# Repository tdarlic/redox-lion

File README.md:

# redox-lion
Wireless redox keyboard based on nRF52840 or similar chips and with lion battery

Chip purchased for BL is: [MS88SF2 Ultra-low Power Wireless BLE 5.0 Module](https://www.aliexpress.com/item/4000101935456.html)
Product page is [here](https://en.minewsemi.com/bluetooth-module/nrf52840ms88sf21)

## Inspiration
- [Wubbo](https://github.com/cacheworks/Wubbo)
- [Dao Choc BLE Keyboard](https://github.com/yumagulovrn/dao-choc-ble)
- [le_chiff_ble](https://github.com/MangoIV/le_chiff_ble) by [MangoIV](https://github.com/MangoIV) - electrical circuit

### Various links
(BlueMicro840 V1.x)[http://nrf52.jpconstantineau.com/docs/bluemicro840_v1/]

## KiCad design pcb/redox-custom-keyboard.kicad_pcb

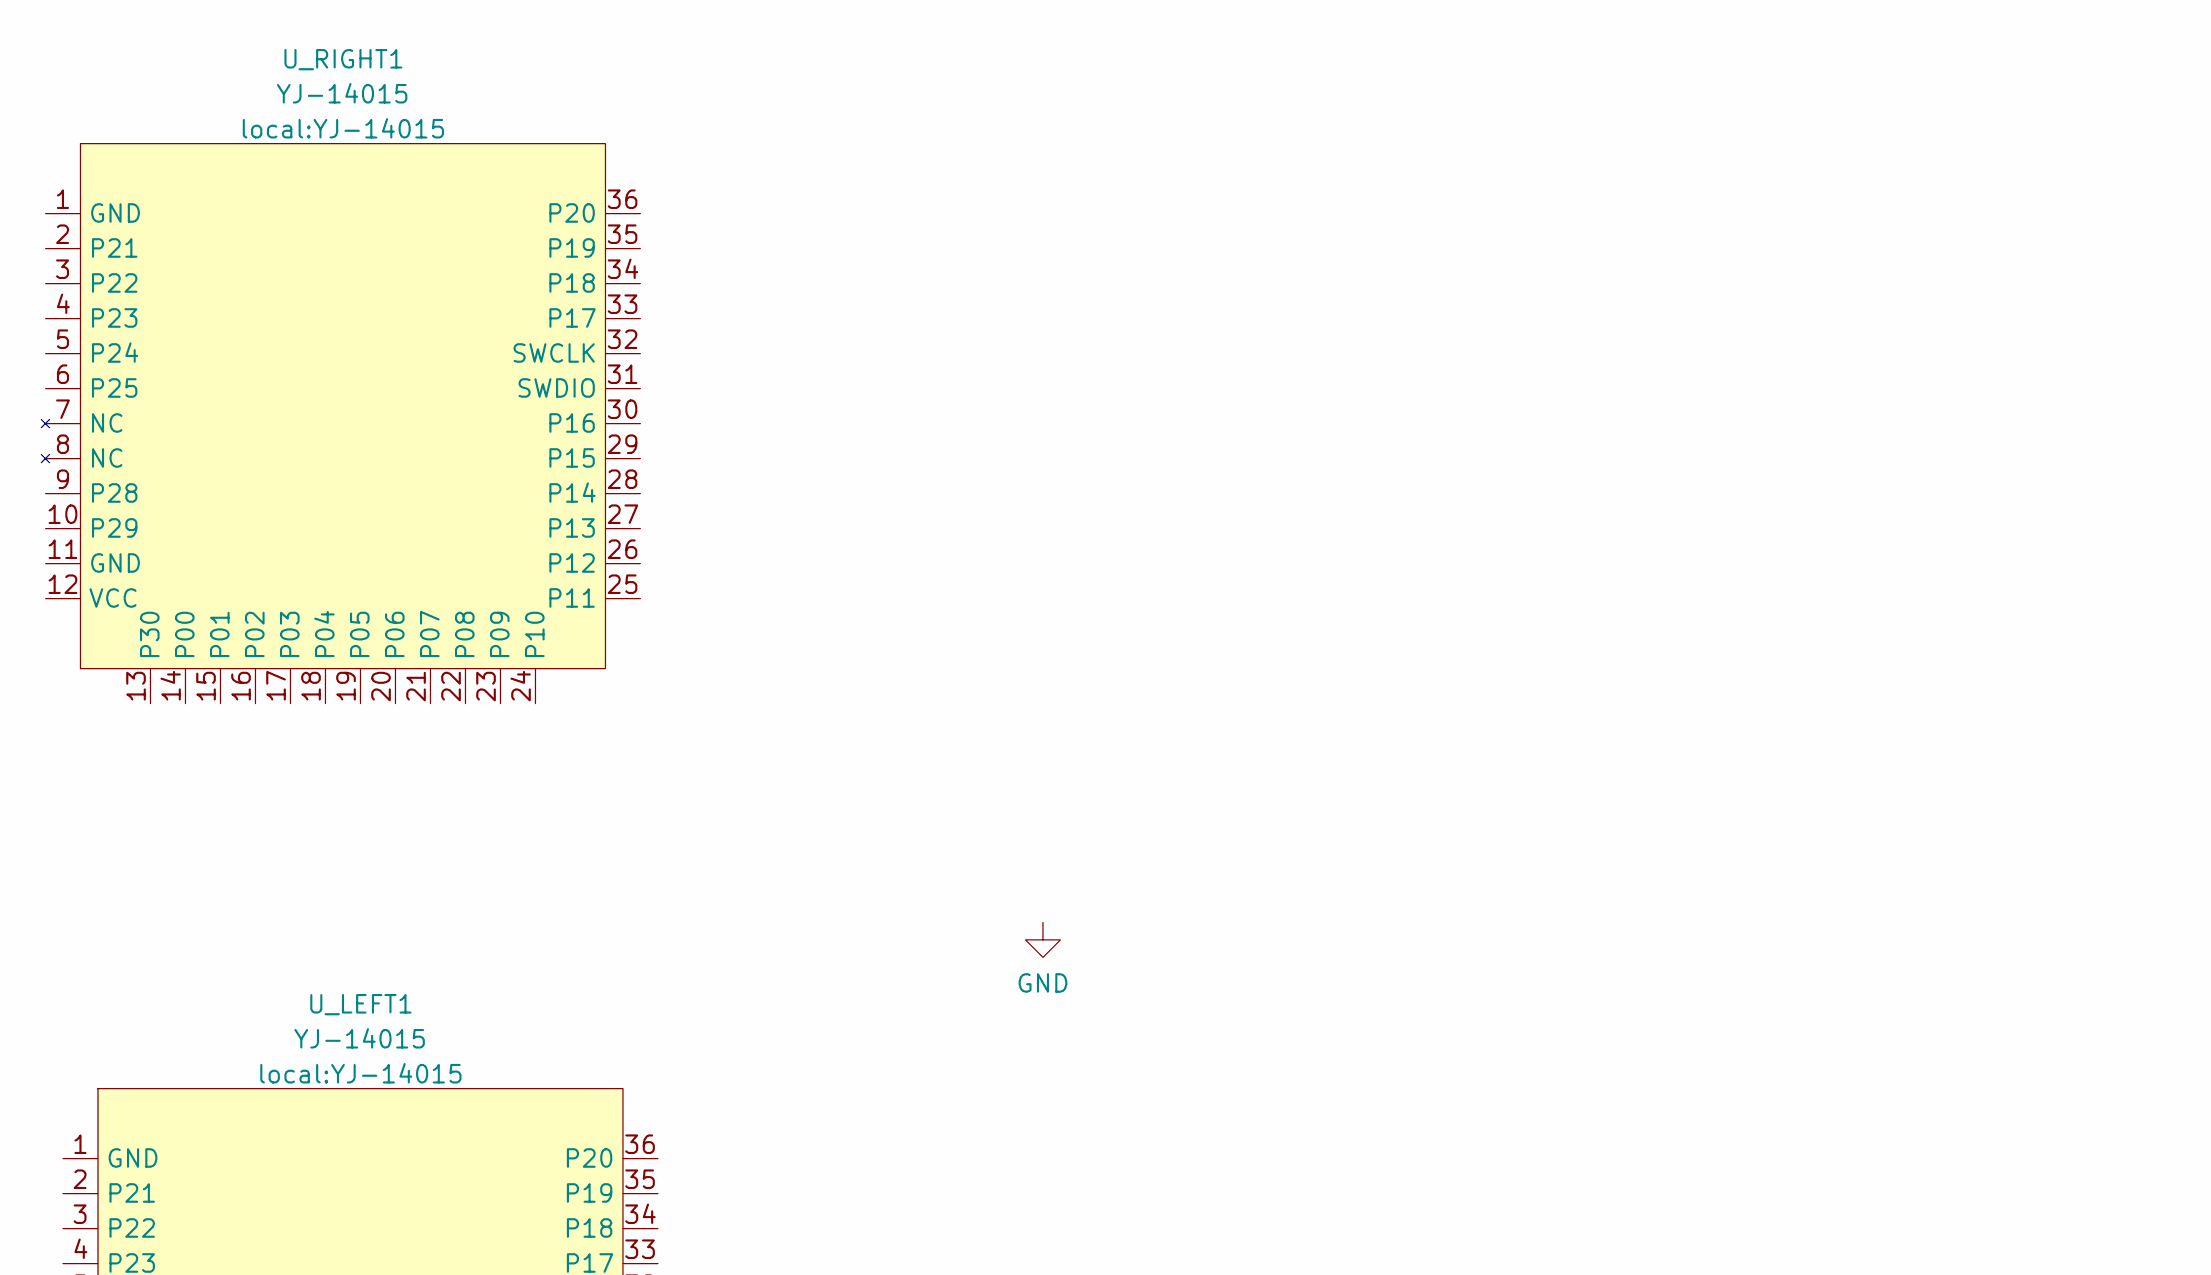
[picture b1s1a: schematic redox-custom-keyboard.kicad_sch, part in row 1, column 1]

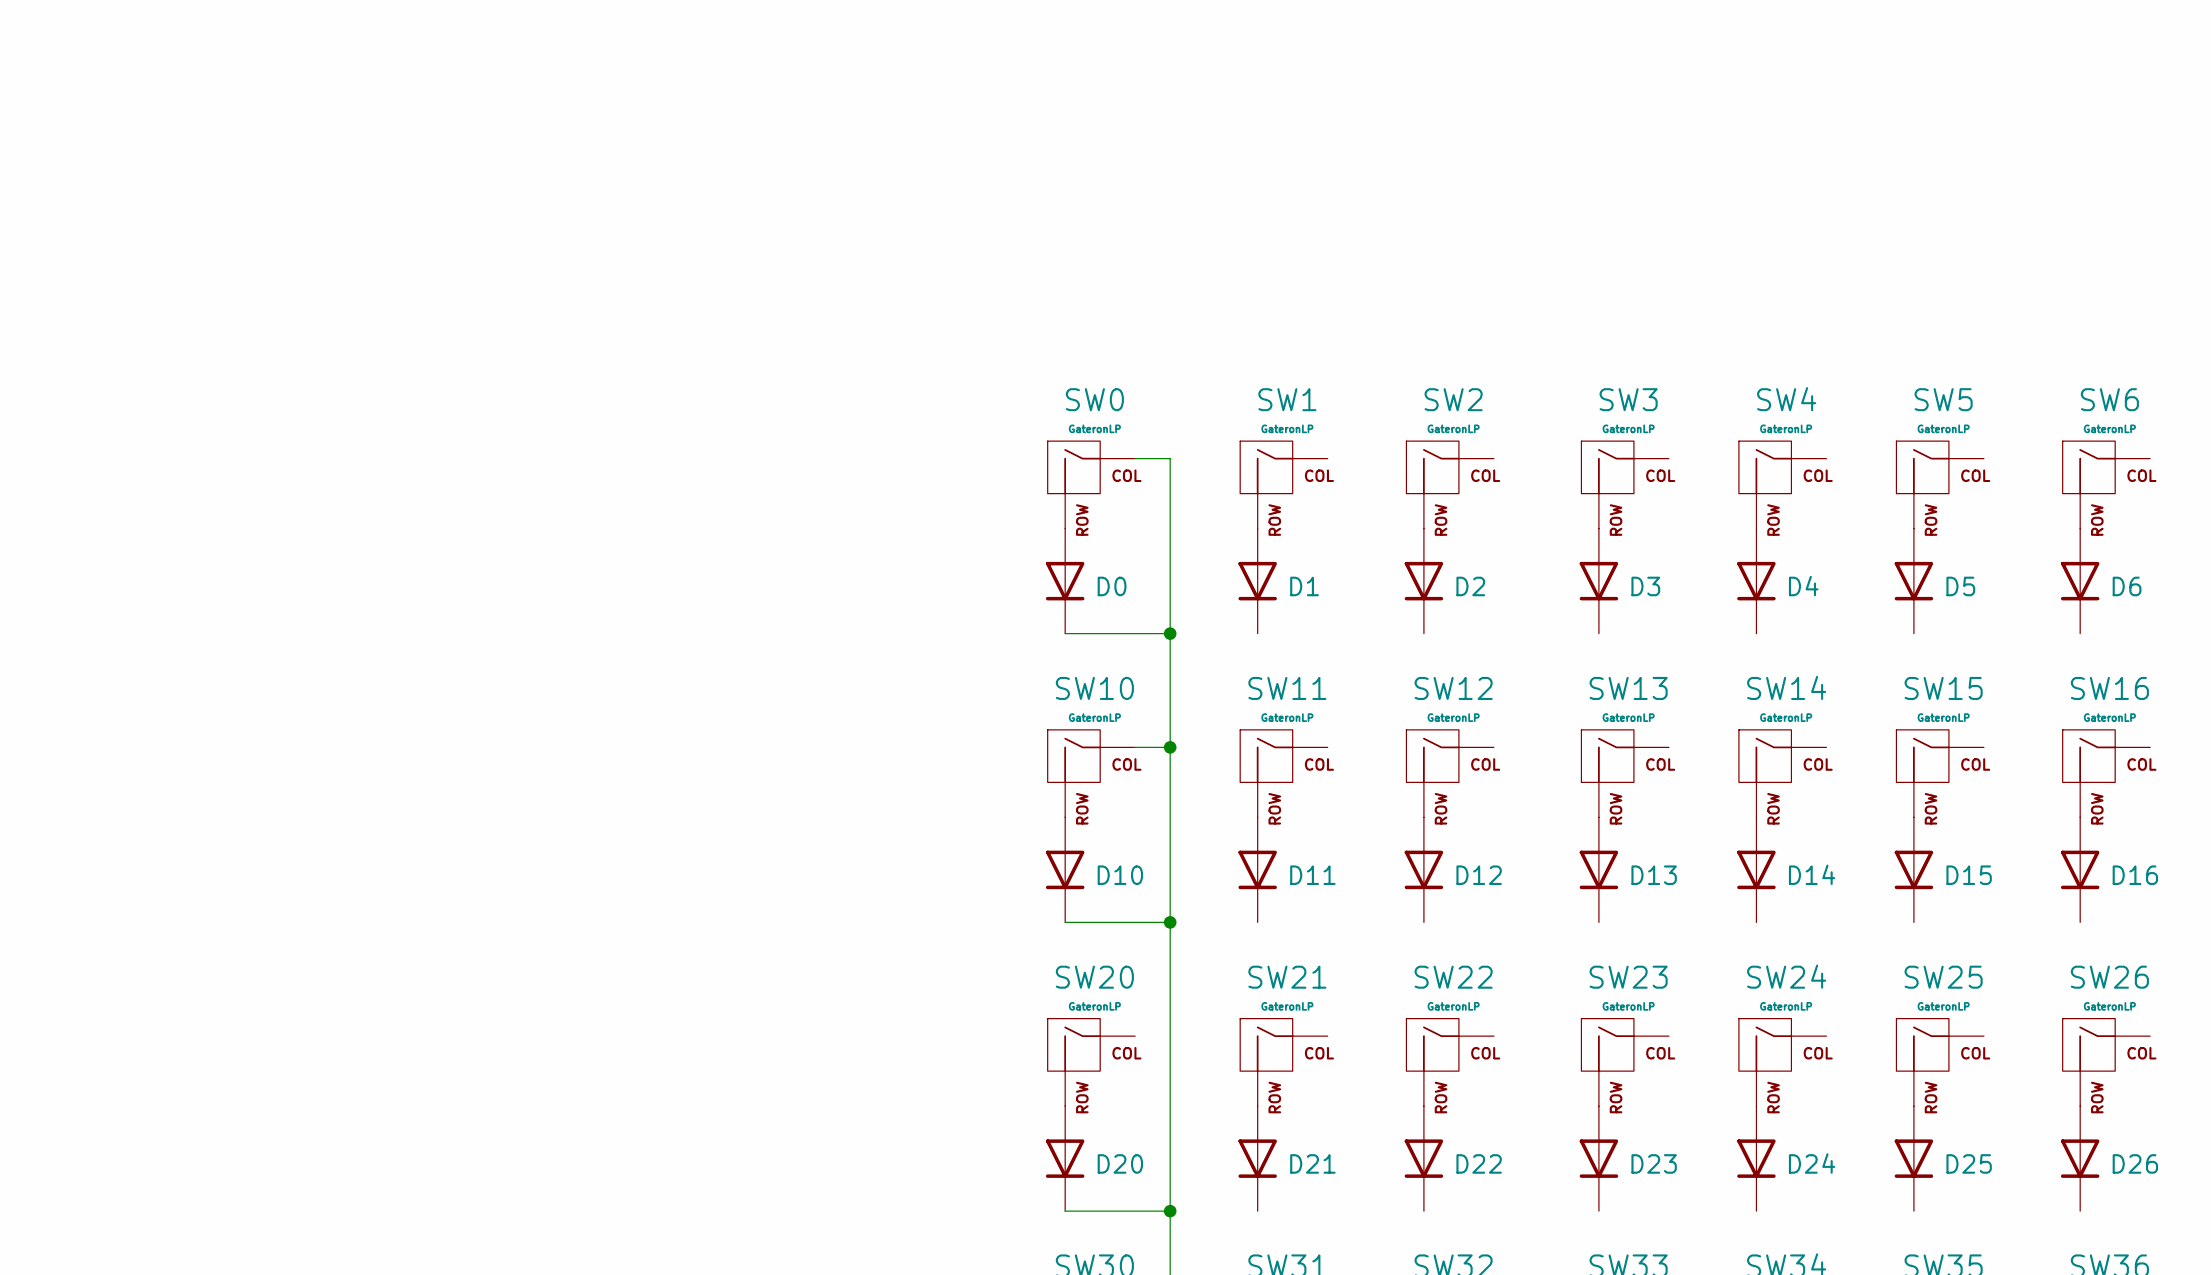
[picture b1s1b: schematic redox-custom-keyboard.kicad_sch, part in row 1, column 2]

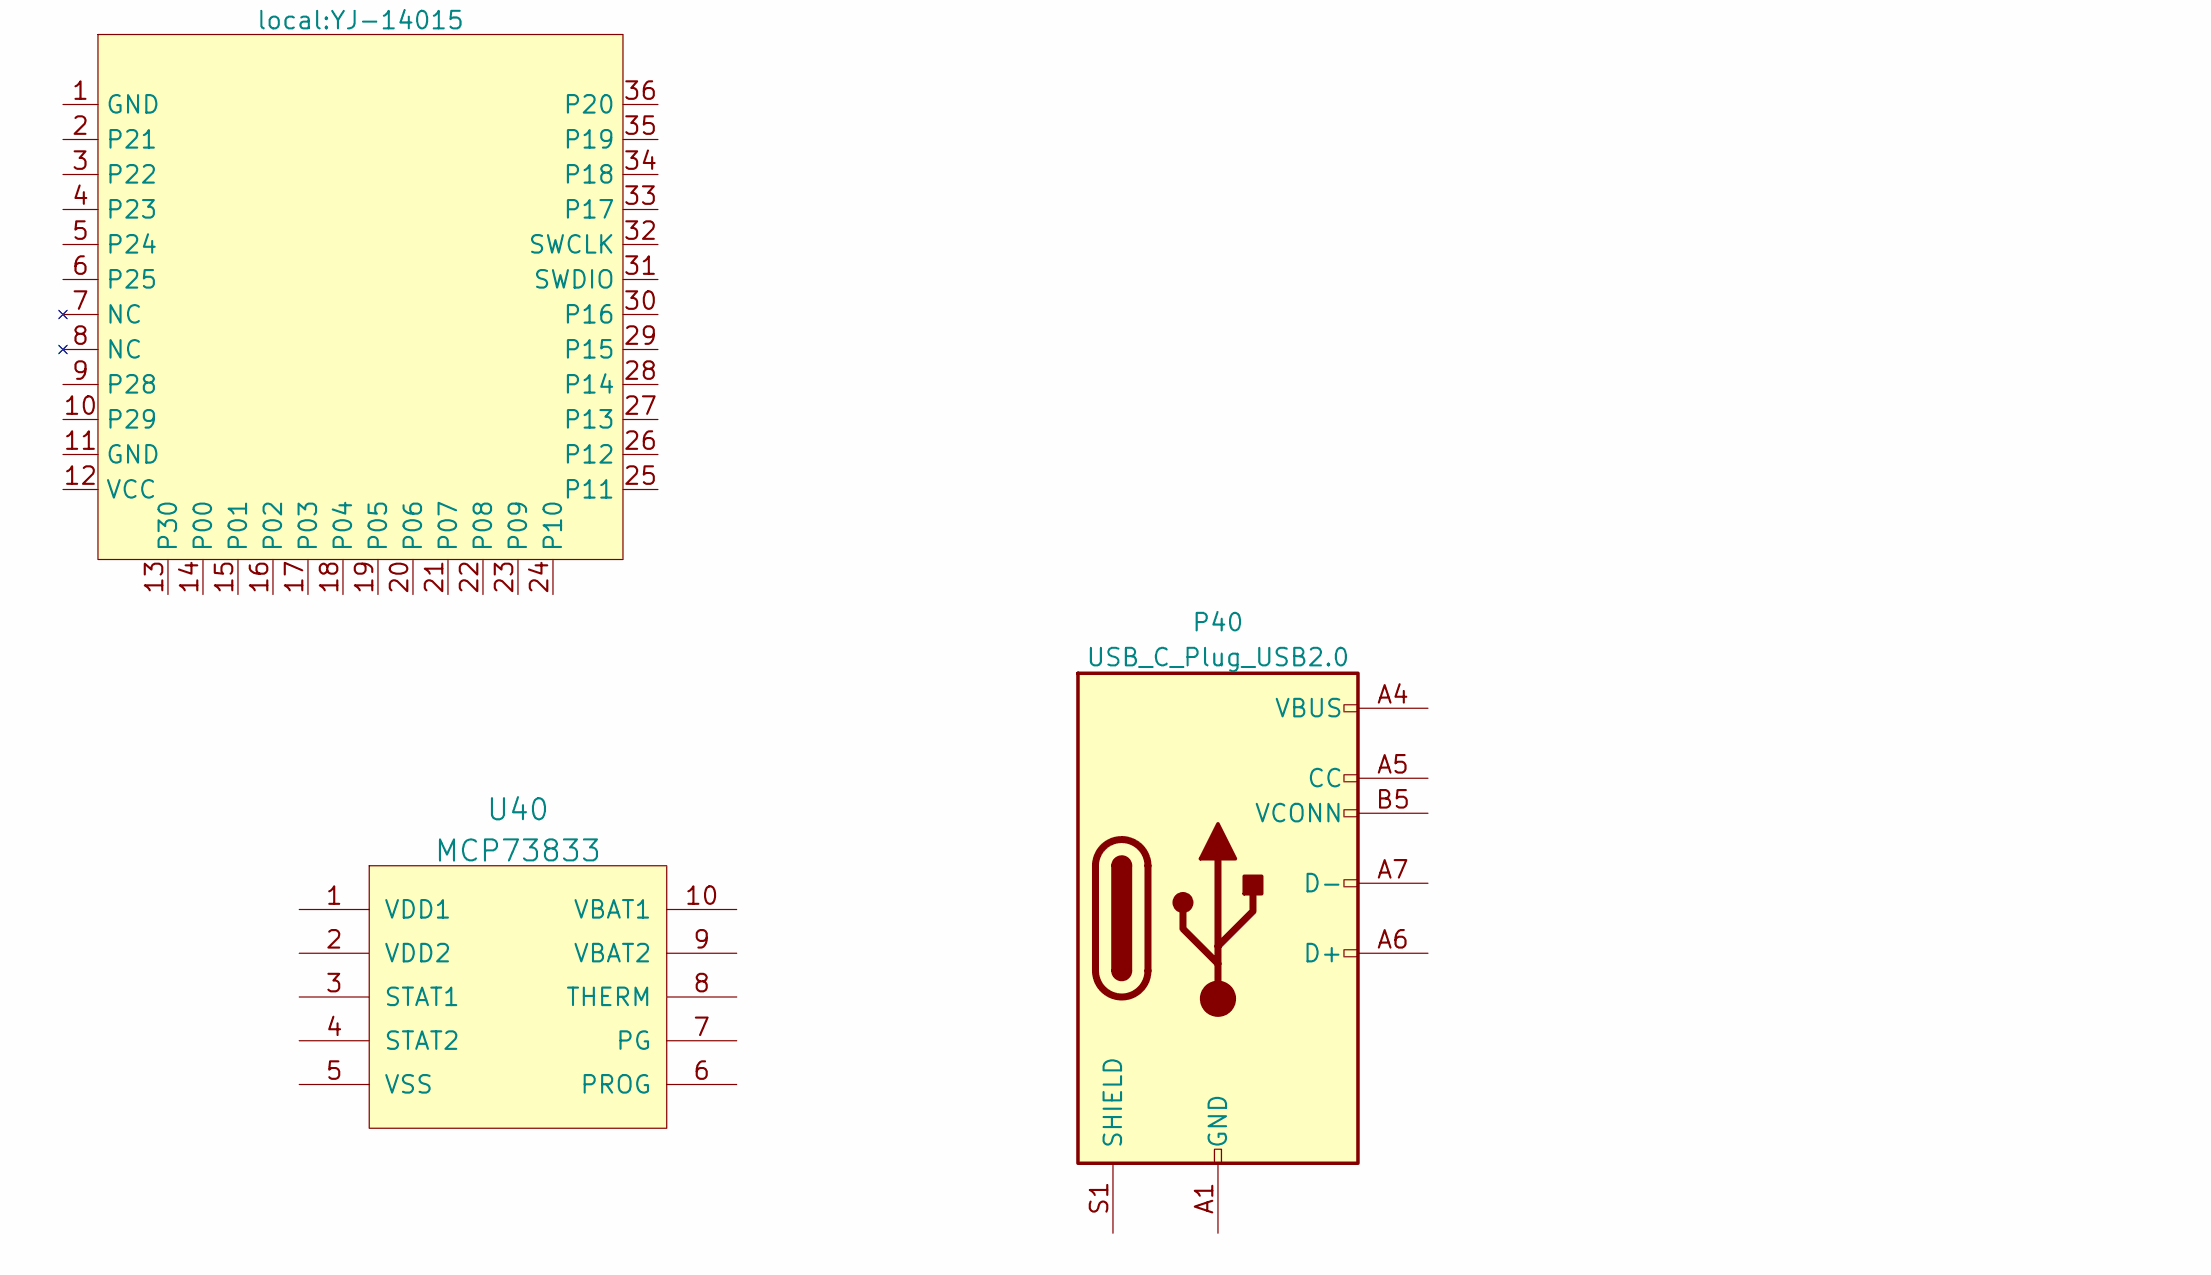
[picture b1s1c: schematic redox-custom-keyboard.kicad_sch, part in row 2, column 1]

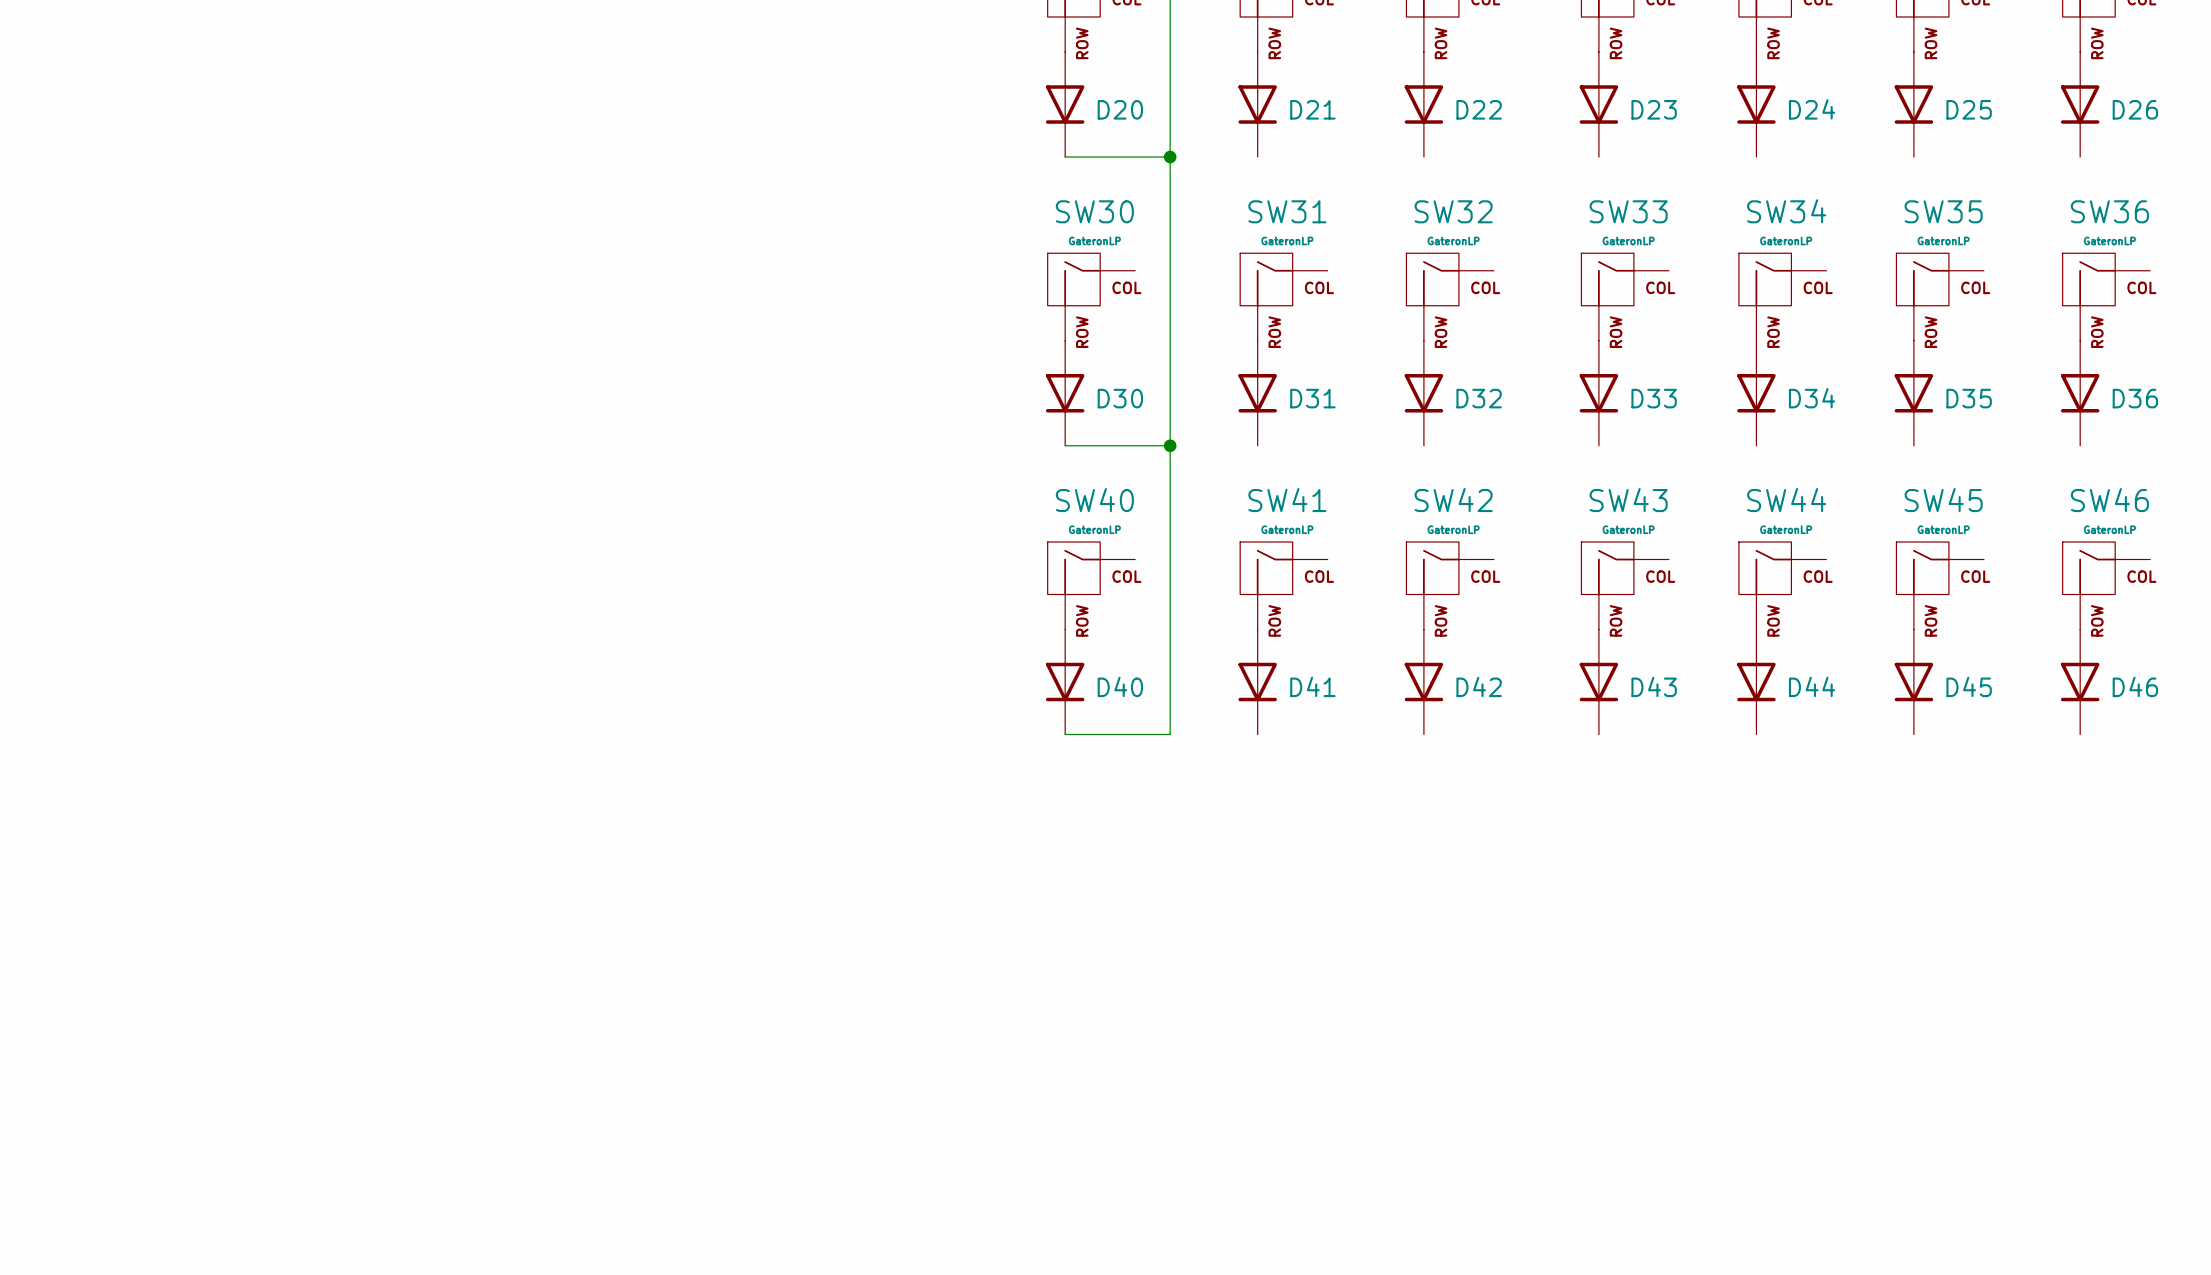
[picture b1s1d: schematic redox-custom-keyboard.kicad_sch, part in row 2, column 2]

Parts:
D0, D1, D2, D3, D4, D5, D6, D10, D11, D12, D13, D14, D15, D16, D20, D21, D22, D23, D24, D25, D26, D30, D31, D32, D33, D34, D35, D36, D40, D41, D42, D43, D44, D45, D46: 1N4148W; D_SOD-123
P40: USB_C_Plug_USB2.0
SW0, SW1, SW2, SW3, SW4, SW5, SW6, SW10, SW11, SW12, SW13, SW14, SW15, SW16, SW20, SW21, SW22, SW23, SW24, SW25, SW26, SW30, SW31, SW32, SW33, SW34, SW35, SW36, SW40, SW41, SW42, SW43, SW44, SW45, SW46: GateronLP; Gateron_low_profile_noled_reversible
U40: MCP73833
U_LEFT1: YJ-14015
U_RIGHT1: YJ-14015

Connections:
unnamed: D0.1 (K), D10.1 (K), D20.1 (K), D30.1 (K), D40.1 (K), SW0.1 (COL), SW10.1 (COL)
unnamed: D0.2 (A), SW0.2 (ROW)
unnamed: D1.2 (A), SW1.2 (ROW)
unnamed: D2.2 (A), SW2.2 (ROW)
unnamed: D3.2 (A), SW3.2 (ROW)
unnamed: D4.2 (A), SW4.2 (ROW)
unnamed: D5.2 (A), SW5.2 (ROW)
unnamed: D6.2 (A), SW6.2 (ROW)
unnamed: D10.2 (A), SW10.2 (ROW)
unnamed: D11.2 (A), SW11.2 (ROW)
unnamed: D12.2 (A), SW12.2 (ROW)
unnamed: D13.2 (A), SW13.2 (ROW)
unnamed: D14.2 (A), SW14.2 (ROW)
unnamed: D15.2 (A), SW15.2 (ROW)
unnamed: D16.2 (A), SW16.2 (ROW)
unnamed: D20.2 (A), SW20.2 (ROW)
unnamed: D21.2 (A), SW21.2 (ROW)
unnamed: D22.2 (A), SW22.2 (ROW)
unnamed: D23.2 (A), SW23.2 (ROW)
unnamed: D24.2 (A), SW24.2 (ROW)
unnamed: D25.2 (A), SW25.2 (ROW)
unnamed: D26.2 (A), SW26.2 (ROW)
unnamed: D30.2 (A), SW30.2 (ROW)
unnamed: D31.2 (A), SW31.2 (ROW)
unnamed: D32.2 (A), SW32.2 (ROW)
unnamed: D33.2 (A), SW33.2 (ROW)
unnamed: D34.2 (A), SW34.2 (ROW)
unnamed: D35.2 (A), SW35.2 (ROW)
unnamed: D36.2 (A), SW36.2 (ROW)
unnamed: D40.2 (A), SW40.2 (ROW)
unnamed: D41.2 (A), SW41.2 (ROW)
unnamed: D42.2 (A), SW42.2 (ROW)
unnamed: D43.2 (A), SW43.2 (ROW)
unnamed: D44.2 (A), SW44.2 (ROW)
unnamed: D45.2 (A), SW45.2 (ROW)
unnamed: D46.2 (A), SW46.2 (ROW)
unnamed: P40.A1 (GND), P40.A12 (GND), P40.B1 (GND), P40.B12 (GND)
unnamed: P40.A4 (VBUS), P40.A9 (VBUS), P40.B4 (VBUS), P40.B9 (VBUS)

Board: 2 copper layers, 70 parts (0 on the bottom side), 36 nets, no tracks yet.

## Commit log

2024-01-23 Add changes found on Shuttle
2024-11-09 Add comments and references to other keyboard as inspiration
2024-11-12 Add links to chip and datasheets
